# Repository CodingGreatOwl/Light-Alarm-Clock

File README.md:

# LightAlarmClock

A hardware-software alarm clock system that combines an Android app, BLE communication, and an ESP32 firmware controller to trigger a pre-alarm light sequence before the alarm rings.

This project demonstrates end-to-end product engineering across mobile, embedded firmware, and electronics design.

## Why this project

Traditional alarms wake you up abruptly with sound. LightAlarmClock introduces a softer wake-up flow:

1. 10 minutes before alarm: Android app sends a BLE command
2. ESP32 receives command: firmware starts a timed IR/light transmission sequence
3. Alarm time: full alarm rings on phone with dismiss/snooze UI

This creates a practical blueprint for a smart alarm + ambient wake-up device.

## System Architecture

### 1) Android App (`Android/`)
- Built with Kotlin + Jetpack Compose
- Vibecoded Android implementation focused on fast iteration and feature validation
- Lets users:
  - create/edit/delete alarms
  - configure recurring schedules
  - choose ringtone
  - toggle vibration/notification
  - configure BLE target (device address, service UUID, characteristic UUID, message)
- Uses `AlarmManager.setExactAndAllowWhileIdle` for precise alarms
- Triggers a BLE foreground service (`BleMessageService`) 10 minutes before alarm
- Launches a full-screen alarm activity (`AlarmActivity`) and ringing service (`AlarmRingingService`) at alarm time

### 2) ESP32 Firmware (`Rust - ESP32/`)
- Built in Rust using `esp-idf-svc` + `esp32-nimble`
- Exposes a custom BLE service/characteristic
- On write, starts a state-machine-driven transmission (PWM + timer interrupts)
- Generates a modulated sequence (38.2 kHz carrier) suitable for IR/light control workflows

### 3) Hardware Shield (`LED_shield/`)
- KiCad project for custom LED/IR driver shield
- Includes:
  - schematic (`.kicad_sch`)
  - PCB layout (`.kicad_pcb`)
  - Gerber outputs (`GBR/`)
  - BOM (`BOM.csv`)
- Components include an IR LED (LD271), regulator (LM7805), and supporting passives/connectors

## Key Features

- End-to-end alarm pipeline from mobile UI to physical actuation
- Foreground services for reliable background BLE and alarm behavior
- Lock-screen alarm UX with Snooze / Dismiss actions
- Recurring alarm scheduling and day selection
- Hardware manufacturing assets included (Gerbers + BOM)

## Tech Stack

### Android
- Kotlin
- Jetpack Compose (Material 3)
- Android AlarmManager / BroadcastReceiver / Foreground Service

### Embedded
- Rust (edition 2021)
- `esp-idf-svc`
- `esp32-nimble` (BLE stack)

### Hardware
- KiCad (schematic + PCB)
- Through-hole + connector-based shield design

## Repository Structure

```text
LightAlarmClock/
├── Android/           # Kotlin Android app (UI, alarms, BLE client)
├── Rust - ESP32/      # ESP32 Rust firmware (BLE peripheral + signal generation)
├── LED_shield/        # KiCad hardware design + Gerbers + BOM
└── LICENSE            # GPL-3.0
```

## Getting Started

## Prerequisites

- Android Studio (latest stable)
- Android device running API 33+ (for current app config)
- ESP32 development board
- Rust + esp-idf toolchain for ESP32 builds
- BLE-capable phone and ESP32 in range

## 1) Run Android App

```bash
cd Android
./gradlew assembleDebug
```

Then install from Android Studio or via adb.

## 2) Flash ESP32 Firmware

From `Rust - ESP32/`, build/flash with your ESP-IDF Rust setup (tooling varies by environment).
The firmware advertises BLE service:

- Service UUID: `6827989e-079a-404f-946a-da39f968ce82`
- Characteristic UUID: `c696a5a1-827f-4df2-8260-5cdc7f0a4f44`

## 3) Configure BLE in App

In the app:
- Open Bluetooth Settings
- Enter ESP32 MAC address
- Confirm service/characteristic UUIDs
- Set message payload
- Use Test Connection and Send Test Message

## Alarm Flow (Runtime)

1. User schedules alarm in app
2. App registers:
   - main alarm trigger
   - BLE pre-alarm trigger (10 minutes earlier)
3. Pre-alarm fires -> `BlePreAlarmReceiver` starts `BleMessageService`
4. BLE write triggers ESP32 transmission sequence
5. Main alarm fires -> alarm UI + ringing foreground service
6. User snoozes or dismisses

## Recruiter Highlights

This project showcases:

- Cross-domain engineering: mobile + embedded + PCB
- Real-world Android architecture: alarms, receivers, services, lock-screen behavior
- Low-level firmware work: timers, PWM, BLE GATT handling
- System integration mindset: one product, multiple layers, clear signal path
- Product thinking: user-centric wake-up experience, not just a technical demo

## Known Improvements / Roadmap

- Add automated tests (unit + instrumentation) for alarm scheduling edge cases
- Improve BLE retry/backoff and connection lifecycle handling
- Add screenshots/GIFs for app UX in this README
- Add hardware bring-up and calibration guide
- Harden production alarm reliability across OEM battery optimizations

## License

This project is licensed under GNU GPL v3.0.
See [`LICENSE`](LICENSE).

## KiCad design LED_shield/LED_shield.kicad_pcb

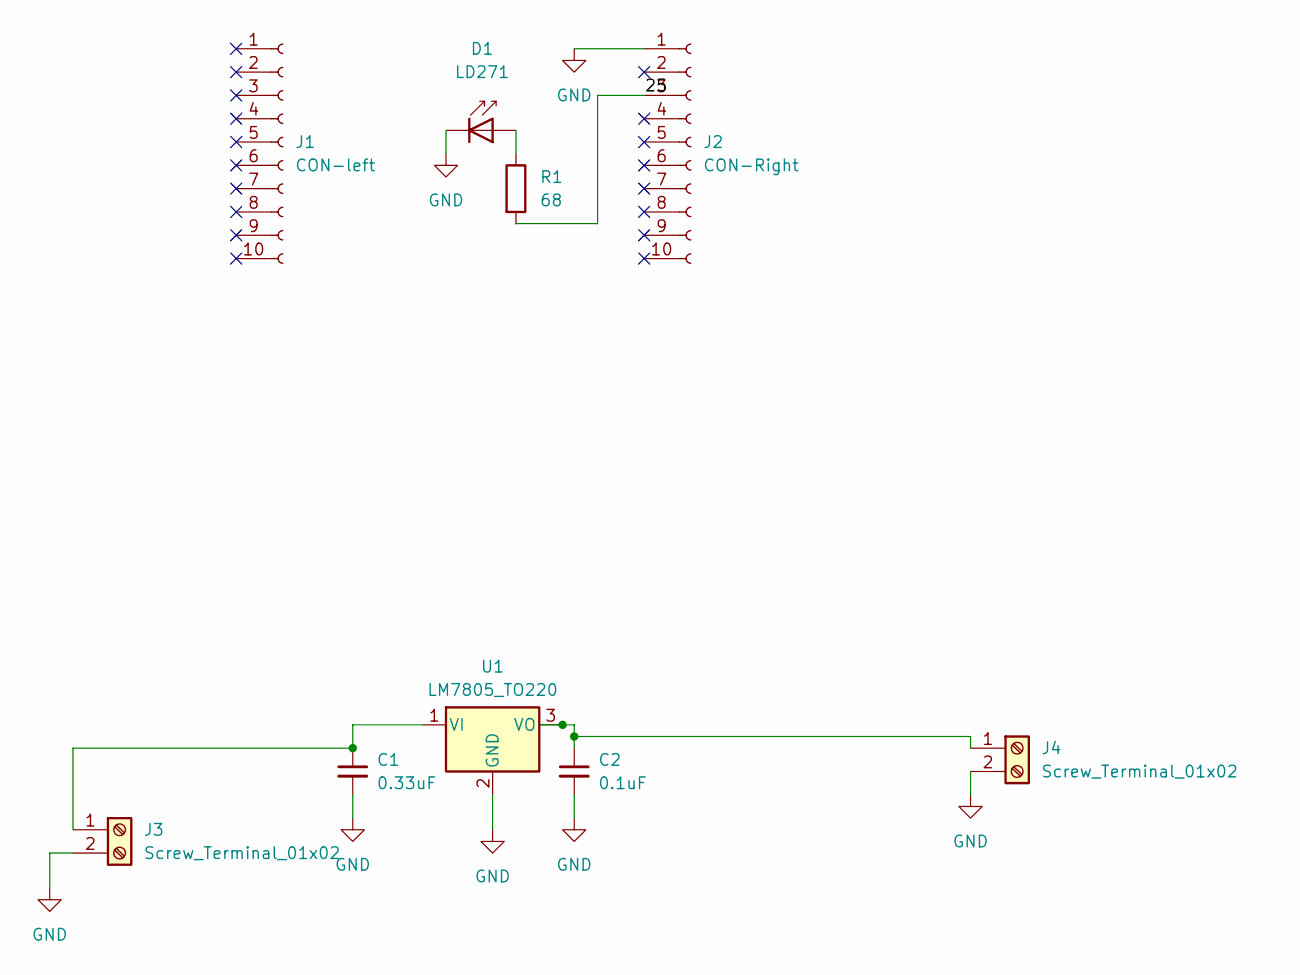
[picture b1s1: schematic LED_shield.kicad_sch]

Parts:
C1: 0.33uF; C_Rect_L7.0mm_W2.0mm_P5.00mm
C2: 0.1uF; C_Rect_L7.0mm_W2.0mm_P5.00mm
D1: LD271; LED_D5.0mm_IRGrey
J1: CON-left; PinSocket_1x10_P2.54mm_Vertical
J2: CON-Right; PinSocket_1x10_P2.54mm_Vertical
J3, J4: Screw_Terminal_01x02; TerminalBlock_MaiXu_MX126-5.0-02P_1x02_P5.00mm
R1: 68; R_Axial_DIN0411_L9.9mm_D3.6mm_P15.24mm_Horizontal
U1: LM7805_TO220; TO-220-3_Vertical

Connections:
/25: J2.3, R1.2
GND: C1.2, C2.2, D1.1 (K), J2.1, J3.2, J4.2, U1.2 (GND)
unnamed: D1.2 (A), R1.1
unnamed: C1.1, J3.1, U1.1 (VI)
unnamed: C2.1, J4.1, U1.3 (VO)

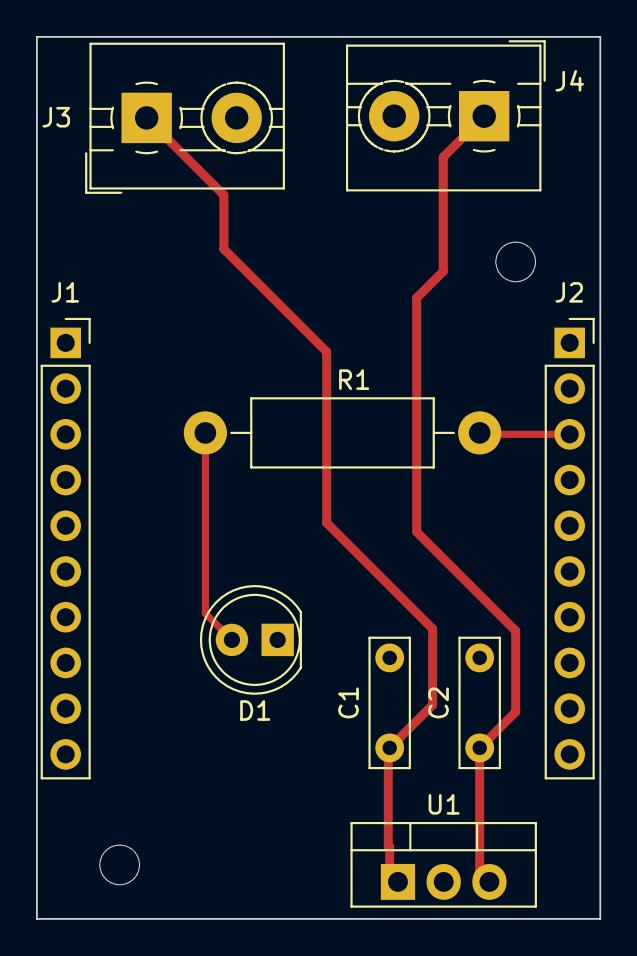
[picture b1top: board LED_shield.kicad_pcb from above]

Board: 2 copper layers, 31.3 x 49.0 mm, 9 parts (0 on the bottom side), 5 nets.

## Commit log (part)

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2025-08-16 Fix refresh of alarm issue
2025-10-01 BLE failing config
2025-10-02 Fix ble communication
2025-10-02 Fix alarm
2025-10-16 Alarm rings outside of the app
2025-10-17 Alarm rings on the speakers
2025-10-17 Alarm rings with the correct ringtone
2025-10-17 Remove unnesseary imports
2025-10-17 Remove some warnings
2025-10-17 Disconnect from the ble server after writing the value
2026-01-21 Work on the locked screen
2026-01-21 Add vibration in alarm when screen is locked
2026-01-21 Cosmetic changes
2026-01-21 Remove unused import
2026-01-21 dismiss button in the notifications
